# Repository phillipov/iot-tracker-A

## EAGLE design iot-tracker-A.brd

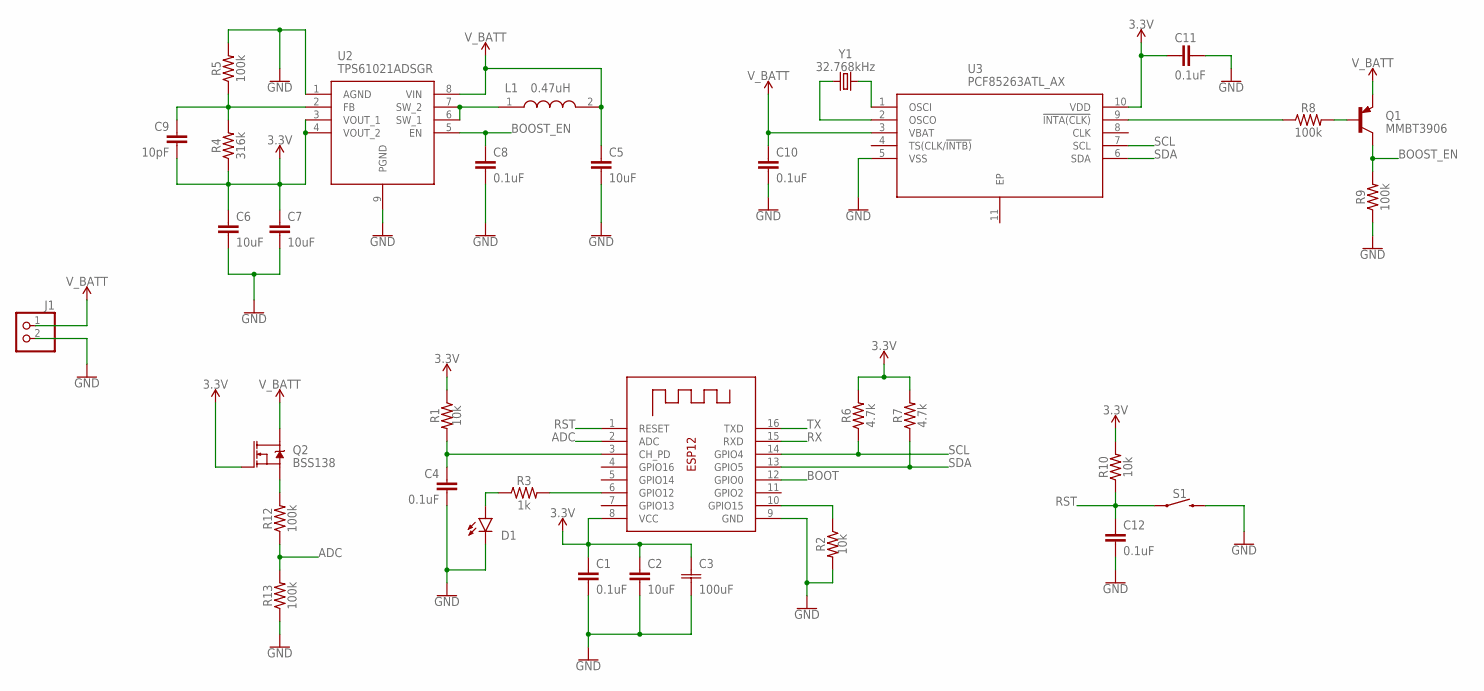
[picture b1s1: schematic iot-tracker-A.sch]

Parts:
C1, C4, C8, C10, C11, C12: 0.1uF; 0603
C2, C5, C6, C7: 10uF; 0603
C3: 100uF; F93-C
C9: 10pF; 0603
D1: LED0603; LED-0603
J1: PINHD-1X2; 1X02
L1: 0.47uH; INDC2520X120N
Q1: MMBT3906; SOT23-BEC
Q2: BSS138; SOT23-3
R1, R2, R10: 10k; 0603
R3: 1k; 0603
R4: 316k; 0603
R5, R8, R9, R12, R13: 100k; 0603
R6, R7: 4.7k; 0603
S1: MOMENTARY-SWITCH-SPST-SMD-4.6X2.8MM; TACTILE_SWITCH_SMD_4.6X2.8MM
U1: ESP-12
U2: TPS61021ADSGR; SON50P200X200X80-9N
U3: PCF85263ATL_AX; SON50P260X260X50-11N
Y1: 32.768kHz; CRYSTAL-SMD-3.2X1.5MM

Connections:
3.3V: C1.1, C2.1, C3.1, C6.1, C7.1, C9.2, C11.2, Q2.1 (G), R1.1, R4.1, R6.2, R7.2, R10.2, U1.8 (VCC), U2.3 (VOUT_1), U2.4 (VOUT_2), U3.10 (VDD)
ADC: R12.1, R13.2, U1.2 (ADC)
BOOST_EN: C8.1, Q1.C, R9.2, U2.5 (EN)
BOOT: U1.12 (GPIO0)
ESP_EN: C4.1, R1.2, U1.3 (CH_PD)
FB: C9.1, R4.2, R5.1, U2.2 (FB)
GND: C1.2, C2.2, C3.2, C4.2, C5.2, C6.2, C7.2, C8.2, C10.2, C11.1, C12.2, D1.C, J1.2, R2.2, R5.2, R9.1, R13.1, S1.3 (2), S1.4 (2), U1.9 (GND), U2.1 (AGND), U2.9 (PGND), U3.5 (VSS)
INTA: R8.1, U3.9 (!INTA(CLK))
IO15: R2.1, U1.10 (GPIO15)
IO_LED: R3.2, U1.6 (GPIO12)
LED_AN: D1.A, R3.1
MOSFET_S: Q2.2 (S), R12.2
OSCI: U3.1 (OSCI), Y1.P$2 (2)
OSCO: U3.2 (OSCO), Y1.P$1 (1)
PNP_B: Q1.B, R8.2
RST: C12.1, R10.1, S1.1, S1.2 (1), U1.1 (RESET)
RX: U1.15 (RXD)
SCL: R6.1, U1.14 (GPIO4), U3.7 (SCL)
SDA: R7.1, U1.13 (GPIO5), U3.6 (SDA)
SW: L1.1, U2.6 (SW_1), U2.7 (SW_2)
TX: U1.16 (TXD)
V_BATT: C5.1, C10.1, J1.1, L1.2, Q1.E, Q2.3 (D), U2.8 (VIN), U3.3 (VBAT)

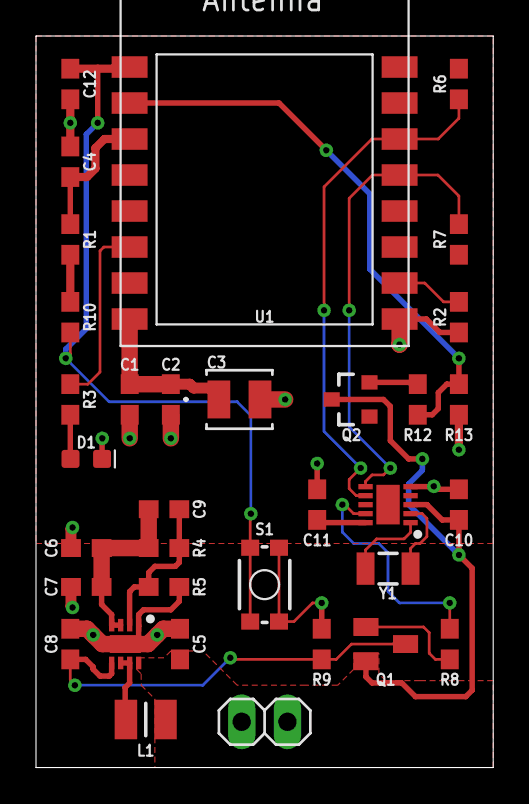
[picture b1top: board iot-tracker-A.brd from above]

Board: 2 copper layers, 25.4 x 40.6 mm, 34 parts (0 on the bottom side), 19 nets.

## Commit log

2019-03-28 Added LED to GPIO4.
2019-04-01 Replaced TPS610986 with MCP1640 boost converter
2019-04-01 Reordered component names and added 3.3V symbol
2019-04-02 Created the board file
2019-04-02 Changed pin header from 2x4 to 1x6
2019-04-03 Moved the circuitry below the ESP module
2019-04-03 Routed all connections and added vias to the ground plane
2019-04-03 Added battery pin headers
2019-04-17 Finished routing 3.3V
2019-04-21 Placed ESP-WROOM-02 on bottom layer
2019-05-05 Laid out all components
2019-05-07 Routed everything and added silkscreen text
2019-05-07 Moved pin headers to top layer and changed silkscreen fonts to vector
2019-05-08 Slightly decreased board size for OSH Park pricing
2019-05-11 Reorganized component placement and consolidated headers into a single 1x8 part
2019-05-14 Adjusted placement and defined net classes
2019-05-27 Unleashed the autorouter
2019-05-29 Routed C1 to ground plane
2019-06-23 Started phasing out the MCP1640 boost converter
2019-06-24 Integrated the TPS61021A into the schematic
2019-06-27 Changed bulk capacitors to tantalum; minor component edits
2019-06-27 Started basic board layout
2019-06-28 Slightly improved board layout
2019-06-30 Partially routed boosting circuitry
2019-06-30 Routed everything but GND
2019-07-22 Finished routing and cleared DRC
2019-07-22 Board is ready for fabrication
2019-07-24 Started integrating the RTC
2019-07-24 Changed crystal device and added the PNP for DRVN
2019-07-24 Fully integrated RTC into the schematic
2019-07-25 Minor component changes and net renaming
2019-07-25 Reordered names and grouped components on the board
2019-07-27 Added buttons for reset and boot options
2019-07-27 Replaced 1x8 header with buttons, screw terminals, and a 1x4 header
2019-07-30 Connected a MOSFET switch and voltage divider to the ADC; connected a capacitor to boost enable pin
2019-07-31 Minor net fixes, partially routed every IC
2019-08-02 Finished all routing
2019-08-05 Cleared all DRC errors and increased ground plane clearance
2019-08-05 Added silkscreen text
2019-08-05 Added the ESP-12F and supporting components
2019-08-06 Added smaller buttons, partially routed board
2019-08-06 Finished routing and added text
2019-08-06 Partially routed a 1-square-inch layout
2019-08-13 Resized board, reordered pinheads, routed entire board
2019-08-13 Replaced all power traces with polygons
2019-08-20 Removed onboard debug connectors
2019-08-20 Partially laid out a cleaner board
2019-08-26 Replaced bulk cap with 100uF, laid out components parallel to ESP
2019-08-29 Finished placement, routing, and polygons

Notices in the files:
parts and their libraries:
SparkFun-Capacitors: Licensing: Creative Commons ShareAlike 4.0 International - https://creativecommons.org/licenses/by-sa/4.0
